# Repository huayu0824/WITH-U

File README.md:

<p align="center">
  
  <em>第一版，一言难尽...</em>
  
  <em>第三版</em>

</p>

<h1 align="center">WITH-U 🤖🧸</h1>

<p align="center">
  <em>我把另一个自己写进了代码里，装进玩偶，让它替我去陪她。</em>
</p>

<p align="center">

</p>

---

**WITH-U** 是一个实体 AI 语音交互玩偶项目。基于 ESP32-S3 构建硬件本体，端到端跑通语音识别→大模型推理→超拟声合成，装进 3D 打印外壳里，让ta变成一个可以抱在怀里说话的存在。

## ✨ 功能一览

| 功能 | 说明 |
|------|------|
| 🎤 **语音对话** | 按住说话，松开自动回复。端到端延迟约 2~4 秒 |
| 🗣️ **超拟声 TTS** | CosyVoice 复刻声音，不是机器人腔 |
| 🖥️ **OLED 显示** | 实时反馈对话状态：听、想、说 |
| 🔄 **OTA 升级** | 远程推送固件，不用拆外壳 |
| 📊 **Web 管理面板** | 日志监控、手动推送语录、系统控制 |
| 💾 **对话记录** | 每条对话自动存到 TF 卡 |
| 🐚 **3D 打印外壳** | 自锁按钮、USB-C 充电、完整外观设计 |

## 📐 架构

```
┌─────────────────────────┐         ┌──────────────────────────────┐
│    ESP32-S3 硬件本体      │         │        FastAPI 后端            │
│                          │         │                              │
│  ┌───────────────────┐   │ HTTP/WS │  ┌────────────────────┐     │
│  │ INMP441 麦克风     │──┼─────────┼──┤ ASR 语音识别       │     │
│  │ MAX98357 扬声器    │──┼─────────┼──┤ → DeepSeek LLM     │     │
│  │ 0.96" OLED        │   │         │  │ → CosyVoice TTS   │     │
│  │ SHT3X 温湿度      │   │         │  └────────────────────┘     │
│  │ TF 卡存储          │   │         │                              │
│  └───────────────────┘   │         │  阿里云 · DeepSeek · DashScope│
│  ┌───────────────────┐   │         └──────────────────────────────┘
│  │ WiFi + OTA 升级    │   │
│  │ Web 管理面板(HTML) │   │
│  └───────────────────┘   │
└─────────────────────────┘
```

## 🧰 硬件清单

| 组件 | 型号 | 用途 |
|------|------|------|
| **主控** | ESP32-S3 (16MB Flash + 8MB PSRAM) | 大脑，跑 WiFi + 音频处理 |
| **麦克风** | INMP441 (I2S MEMS) | 拾音 |
| **功放** | MAX98357A (I2S 3W) | 驱动扬声器 |
| **扬声器** | 3W 4Ω | 发声 |
| **显示屏** | 0.96" OLED (SSD1306, I2C) | 状态反馈 |
| **温湿度** | SHT3X (I2C) | 环境感知 |
| **存储** | TF 卡 (SPI 模式) | 对话记录、音频缓存 |
| **电源** | 3.7V 锂电池 + USB-C 充电 | 便携供电 |

## 📁 项目结构

```
WITH-U/
├── esp32_voice_assistant/        # ESP32-S3 固件 (Arduino/PlatformIO)
│   ├── esp32_voice_assistant.ino  # 主程序
│   ├── config.h                   # 硬件配置
│   ├── oled_display.h             # OLED 驱动
│   ├── sd_card.h                  # TF 卡读写
│   ├── sensors.h                  # 温湿度传感器
│   ├── ota_update.h               # OTA 远程升级
│   ├── server/                    # 板载 Web 服务 + 管理面板
│   ├── gerber_output/             # PCB Gerber 文件
│   └── tools/                     # 音频处理工具
├── my-ai-backend/                # AI 后端服务 (FastAPI)
│   ├── main.py                    # API 入口
│   ├── stt.py                     # 阿里云语音识别
│   ├── llm.py                     # DeepSeek 对话
│   ├── tts.py                     # CosyVoice 语音合成
│   └── config.example.py          # 密钥配置模板
├── 386f0e17-a757-40c0-8236-fc20f3f3096d.png  # 项目封面
├── README.md
└── LICENSE
```

## 🚀 快速开始

### 前置条件

- Python 3.10+
- PlatformIO (VS Code 插件或 CLI)
- ESP32-S3 开发板 + INMP441 + MAX98357A
- 阿里云 / DeepSeek / DashScope API 密钥

### 1️⃣ 后端部署

```bash
cd my-ai-backend
pip install -r requirements.txt

# 配置密钥
cp config.example.py .env
# 编辑 .env，填入你的阿里云、DeepSeek、DashScope 密钥

python main.py
```

后端默认运行在 `http://localhost:8000`。

### 2️⃣ 固件烧录

用 VS Code 打开 `esp32_voice_assistant/`，PlatformIO 会自动识别：

```bash
cd esp32_voice_assistant
pio run -t upload
```

或者直接串口烧录编译好的固件。

### 3️⃣ 硬件接线

参考 `config.h` 中的引脚定义：

| 外设 | 引脚 |
|------|------|
| INMP441 麦克风 | BCLK=5, WS=4, DIN=6 |
| MAX98357A 扬声器 | BCLK=15, WS=16, DOUT=7 |
| 按钮 | IO0 (GND 触发) |
| OLED (I2C) | SDA=41, SCL=42 |
| SHT3X (I2C) | 0x44 |
| TF 卡 (SPI) | CS=10, MOSI=11, SCK=12, MISO=13 |

### 4️⃣ 连接玩偶

按住按钮说话，松开后自动发送到后端 → AI 回复 → 扬声器播放。

## 💡 项目起源

> 重庆到山东，一千多公里。
> 见不到面的时候，就让另一个我去陪她。
> **小小倪**是另一个我，替我在她身边说一声 "我在"。

项目名 **WITH-U** —— 和你在一起。

## 📄 License

[MIT](LICENSE) — 随意使用，保留出处即可。

---

<p align="center">
  <a href="https://github.com/huayu0824/WITH-U/issues">反馈问题</a> ·
  <a href="https://github.com/huayu0824/WITH-U/discussions">讨论交流</a>
</p>

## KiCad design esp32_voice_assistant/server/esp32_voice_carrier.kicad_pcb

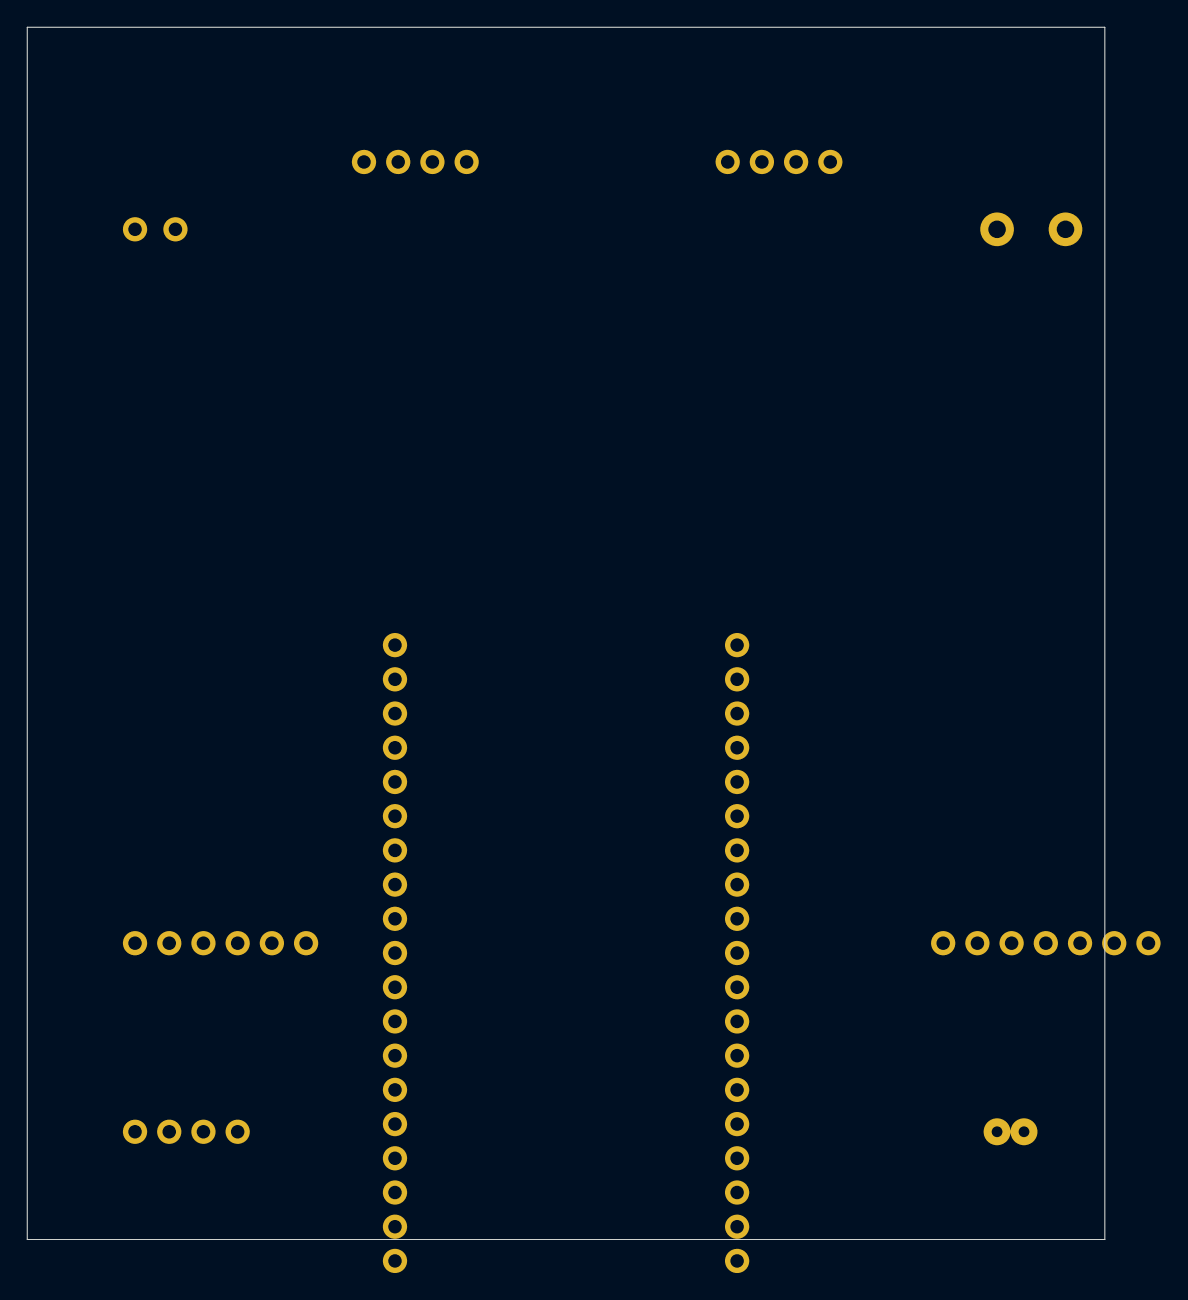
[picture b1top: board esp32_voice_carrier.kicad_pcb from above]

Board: 2 copper layers, 80.0 x 90.0 mm, 9 parts (0 on the bottom side), 11 nets, no tracks yet.

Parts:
BAT1: BATTERY; JST_PH_B2B-PH-K_1x02_P2.0mm_Vertical
J_CHG: CHARGER; PinHeader_1x4_P2.54mm_Vertical
J_ESP32: ESP32-S3; PinSocket_2x19_P2.54mm_Vertical
J_MIC: INMP441; PinHeader_1x6_P2.54mm_Vertical
J_OLED: OLED; PinHeader_1x4_P2.54mm_Vertical
J_SHT3X: SHT3X; PinHeader_1x4_P2.54mm_Vertical
J_SPK: MAX98357; PinHeader_1x7_P2.54mm_Vertical
SPK1: SPEAKER; TerminalBlock_bornier-2_P5.08mm
SW1: BTN; SW_SPST_TL3342

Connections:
3V3: J_ESP32.1A, J_ESP32.19B, J_MIC.1, J_OLED.1, J_SHT3X.1
5V: BAT1.1, J_CHG.3, J_ESP32.2B, J_ESP32.17A, J_SPK.1, J_SPK.7
GND: BAT1.2, J_CHG.2, J_CHG.4, J_ESP32.1B, J_ESP32.4A, J_ESP32.18A, J_MIC.2, J_MIC.6, J_OLED.2, J_SHT3X.2, J_SPK.2, J_SPK.6, SPK1.2, SW1.2
I2C_SCL: J_ESP32.3A, J_OLED.4, J_SHT3X.4
I2C_SDA: J_ESP32.2A, J_OLED.3, J_SHT3X.3
MIC_BCLK: J_ESP32.9A, J_MIC.4
MIC_DIN: J_ESP32.11A, J_MIC.3
MIC_WS: J_ESP32.10A, J_MIC.5
SPK_BCLK: J_ESP32.12A, J_SPK.5
SPK_DOUT: J_ESP32.16A, J_SPK.3
SPK_WS: J_ESP32.15A, J_SPK.4

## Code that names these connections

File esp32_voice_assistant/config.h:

// config.h - ESP32-S3 ??????

#ifndef CONFIG_H
#define CONFIG_H

// ===== ????? OTA =====
#define FIRMWARE_VERSION       "1.1.0"
#define OTA_CHECK_INTERVAL_MS  (6UL * 3600UL * 1000UL)   // ? 6 ??????
#define OTA_MANIFEST_URL       "http://129.204.166.180:8000/api/firmware/manifest"

// ===== ?????? =====
#define ENV_LOCAL
// #define ENV_CLOUD

#ifdef ENV_CLOUD
  const char* SERVER_HOST = "your-domain.com";
#else
  const char* SERVER_HOST = "129.204.166.180";
#endif

const int   SERVER_PORT = 8000;

// ===== ?????? server/config.py ??? =====
const char* WS_TOKEN = "doll-token-001";

// ===== I2S ?? =====
// INMP441 ???
#define MIC_BCLK   5
#define MIC_WS     4
#define MIC_DIN    6

// MAX98357A ??
#define SPK_BCLK   15
#define SPK_WS     16
#define SPK_DOUT   7

// ===== ?? =====
#define BTN_PIN    0   // IO0?????
// ===== ???? =====
#define SAMPLE_RATE     16000
#define RECORD_SECONDS  30
#define BUFFER_SIZE     (SAMPLE_RATE * 4 * RECORD_SECONDS + 4096)

// ===== TF ? (SD SPI) =====
#define SD_CS    10
#define SD_MOSI  11
#define SD_SCK   12
#define SD_MISO  13

// ===== ???????????? 1? =====
#define ENABLE_VAD              0
#define ENABLE_AUTO_SLEEP       0
#define ENABLE_SHT3X            1
#define ENABLE_BATTERY_MONITOR  0

// 32-bit INMP441 ? 16-bit ???????????? RMS ????
#define VAD_RMS_THRESHOLD       600
#define VAD_CONFIRM_FRAMES      3
#define VAD_SILENCE_MS          1200

// SHT3X I2C ?????????
#define SENSOR_SDA              41
#define SENSOR_SCL              42
#define SHT3X_ADDRESS           0x44
#define BATTERY_ADC_PIN         1
#define BATTERY_DIVIDER_RATIO   2.0f

#define IDLE_SLEEP_MINUTES      10

#endif

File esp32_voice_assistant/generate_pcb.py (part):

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    # J1 (左): GPIOs    J2 (右): 电源等
    left_pins = {  # J1, 从板子底部开始编号 (靠近USB端朝上)
        1: (2, "3V3"),    # 3V3
        2: (10, "I2C_SDA"),  # GPIO41 = SDA
        3: (11, "I2C_SCL"),  # GPIO42 = SCL
        4: (1, "GND"),
        5: (0, ""),      # GPIO0 = 按钮
        6: (0, ""),      # GPIO1
        7: (0, ""),      # GPIO2
        8: (0, ""),      # GPIO3
        9: (4, "MIC_BCLK"),   # GPIO4/5 实际看板子
        10: (5, "MIC_WS"),
        11: (6, "MIC_DIN"),
        12: (7, "SPK_DOUT"),
        13: (0, ""),
        14: (0, ""),
        15: (8, "SPK_WS"),    # GPIO16
        16: (9, "SPK_BCLK"),  # GPIO15
        17: (3, "5V"),    # VUSB
        18: (1, "GND"),
        19: (0, "EN"),
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
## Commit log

2026-06-23 🎉 init: WITH-U - 为某人而做的AI语音玩偶
    一个基于 ESP32-S3 的实体 AI 语音交互玩偶项目。
    语音对话（ASR + LLM + TTS）、OTA 升级、Web 管理面板、
    3D 打印外壳，全部开源。
2026-06-23 📝 README全面升级 + 增加.gitattributes
2026-06-23 📝 修正项目叙事 + 跨平台兼容优化
2026-06-23 Update README for inclusive language
    Replaced '她' with 'ta' for gender-neutral language.
